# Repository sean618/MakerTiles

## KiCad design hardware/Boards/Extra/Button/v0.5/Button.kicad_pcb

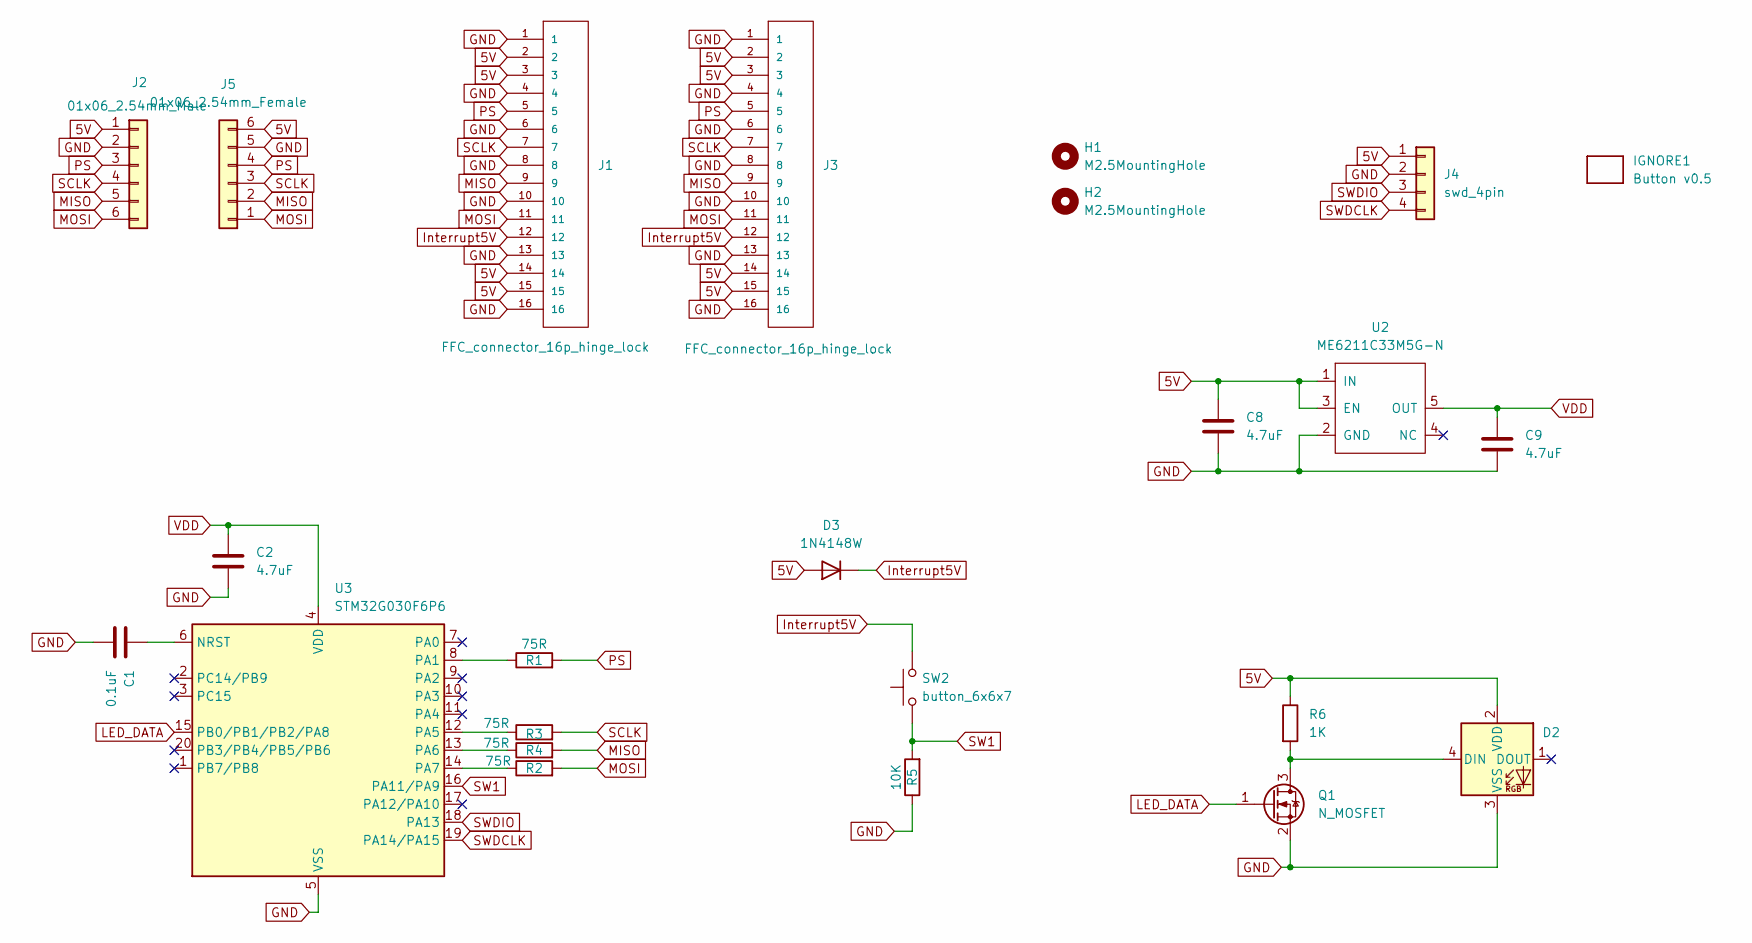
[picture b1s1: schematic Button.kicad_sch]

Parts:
C1: 0.1uF; C_0402_1005Metric
C2, C8, C9: 4.7uF; C_0402_1005Metric
D2: ws2812b_1615; WS2812B_1615
D3: 1N4148W; D_SOD-123
H1, H2: M2.5MountingHole; MountingHole_2.7mm_M2.5_ISO7380
IGNORE1: Button v0.5; BoardText
J1, J3: FFC_connector_16p_hinge_lock
J2: 01x06_2.54mm_Male
J4: swd_4pin; swd_header
J5: 01x06_2.54mm_Female
Q1: N_MOSFET; SOT-23
R1, R2, R3, R4: 75R; R_0402_1005Metric
R5: 10K; R_0402_1005Metric
R6: 1K; R_0402_1005Metric
SW2: button_6x6x7; SW_SPST_PTS645
U2: ME6211C33M5G-N; SOT-23-5
U3: STM32G030F6P6; TSSOP-20_4.4x6.5mm_P0.65mm

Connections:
5V: C8.1, D2.2 (VDD), D3.2 (A), J1.2, J1.3, J1.14, J1.15, J2.1, J3.2, J3.3, J3.14, J3.15, J4.1, J5.6, R6.1, U2.1 (IN), U2.3 (EN)
GND: C1.2, C2.2, C8.2, C9.2, D2.3 (VSS), J1.1, J1.4, J1.6, J1.8, J1.10, J1.13, J1.16, J2.2, J3.1, J3.4, J3.6, J3.8, J3.10, J3.13, J3.16, J4.2, J5.5, Q1.2 (S), R5.1, U2.2 (GND), U3.5 (VSS)
Interrupt5V: D3.1 (K), J1.12, J3.12, SW2.2
LED_DATA: Q1.1 (G), U3.15 (PB0/PB1/PB2/PA8)
MISO: J1.9, J2.5, J3.9, J5.2, R4.2
MOSI: J1.11, J2.6, J3.11, J5.1, R2.2
unnamed: D2.4 (DIN), Q1.3 (D), R6.2
unnamed: C1.1, U3.6 (NRST)
unnamed: R1.1, U3.8 (PA1)
unnamed: R3.1, U3.12 (PA5)
unnamed: R4.1, U3.13 (PA6)
unnamed: R2.1, U3.14 (PA7)
PS: J1.5, J2.3, J3.5, J5.4, R1.2
SCLK: J1.7, J2.4, J3.7, J5.3, R3.2
SW1: R5.2, SW2.1, U3.16 (PA11/PA9)
SWDCLK: J4.4, U3.19 (PA14/PA15)
SWDIO: J4.3, U3.18 (PA13)
VDD: C2.1, C9.1, U2.5 (OUT), U3.4 (VDD)

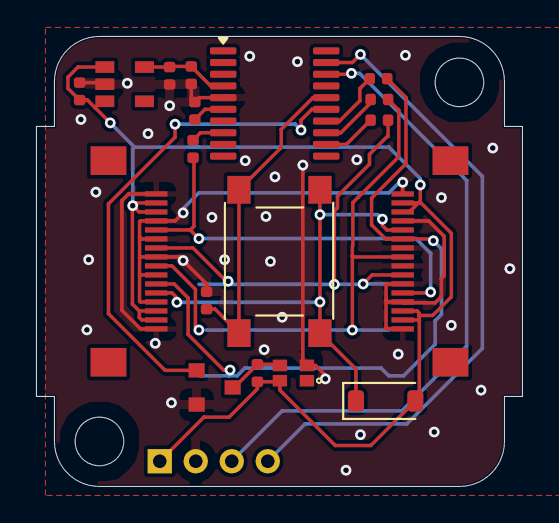
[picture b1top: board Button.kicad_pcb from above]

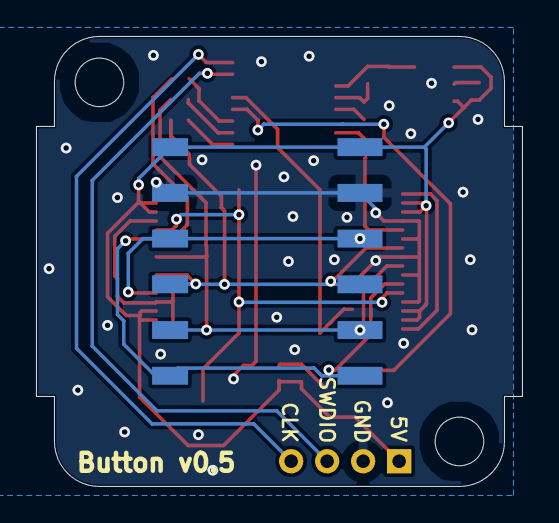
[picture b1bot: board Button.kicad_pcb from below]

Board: 4 copper layers, 27.0 x 25.0 mm, 24 parts (2 on the bottom side), 18 nets.

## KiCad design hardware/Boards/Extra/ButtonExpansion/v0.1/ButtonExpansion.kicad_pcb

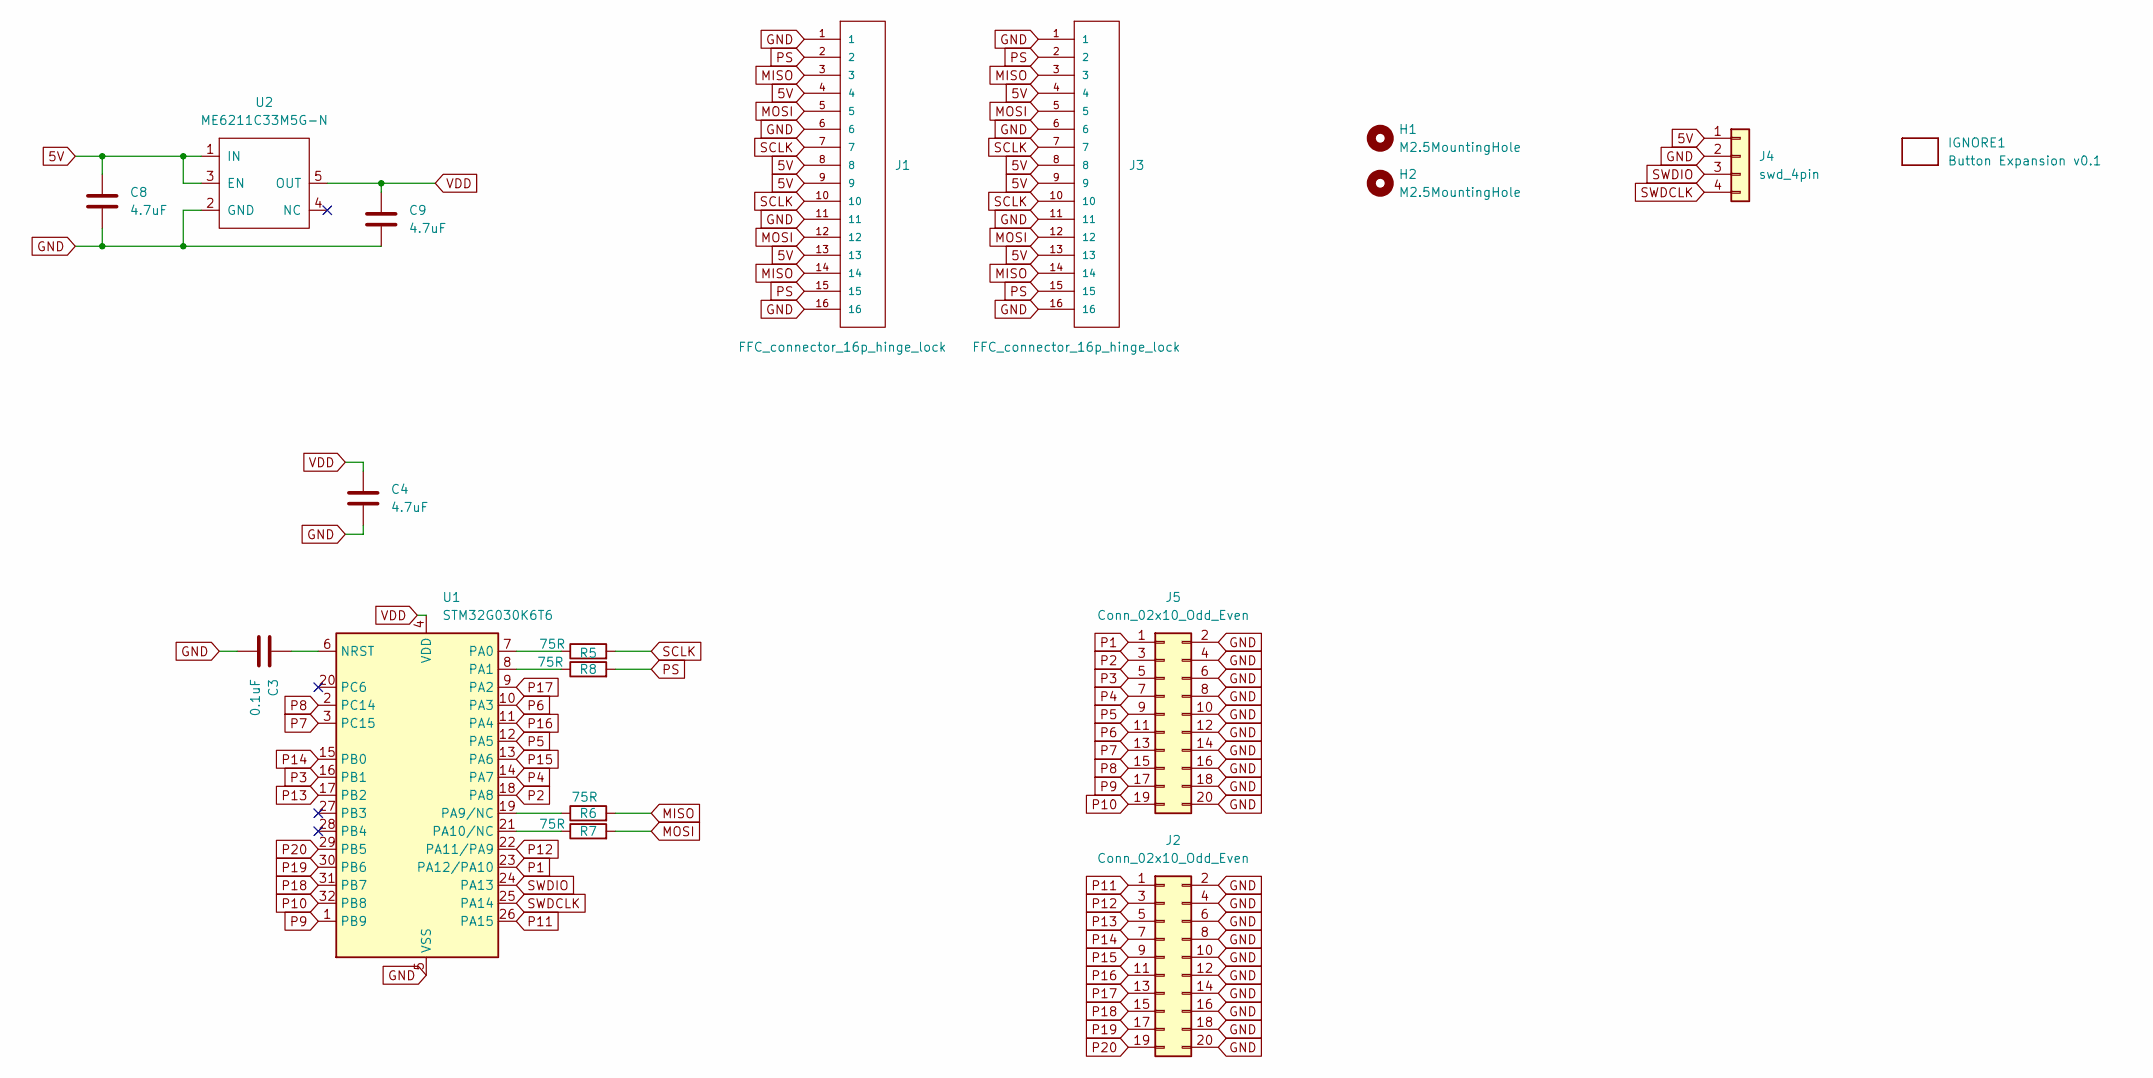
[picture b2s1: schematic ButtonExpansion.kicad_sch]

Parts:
C3: 0.1uF; C_0402_1005Metric
C4, C8, C9: 4.7uF; C_0402_1005Metric
H1, H2: M2.5MountingHole; MountingHole_2.7mm_M2.5_ISO7380
IGNORE1: Button Expansion v0.1; BoardText
J1, J3: FFC_connector_16p_hinge_lock
J2, J5: Conn_02x10_Odd_Even; PinHeader_2x10_P2.54mm_Vertical
J4: swd_4pin; swd_header
R5, R6, R7, R8: 75R; R_0402_1005Metric
U1: STM32G030K6T6; LQFP-32_7x7mm_P0.8mm
U2: ME6211C33M5G-N; SOT-23-5

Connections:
5V: C8.1, J1.4, J1.8, J1.9, J1.13, J3.4, J3.8, J3.9, J3.13, J4.1, U2.1 (IN), U2.3 (EN)
GND: C3.2, C4.2, C8.2, C9.2, J1.1, J1.6, J1.11, J1.16, J2.2, J2.4, J2.6, J2.8, J2.10, J2.12, J2.14, J2.16, J2.18, J2.20, J3.1, J3.6, J3.11, J3.16, J4.2, J5.2, J5.4, J5.6, J5.8, J5.10, J5.12, J5.14, J5.16, J5.18, J5.20, U1.5 (VSS), U2.2 (GND)
MISO: J1.3, J1.14, J3.3, J3.14, R6.2
MOSI: J1.5, J1.12, J3.5, J3.12, R7.2
unnamed: C3.1, U1.6 (NRST)
unnamed: R5.1, U1.7 (PA0)
unnamed: R8.1, U1.8 (PA1)
unnamed: R6.1, U1.19 (PA9/NC)
unnamed: R7.1, U1.21 (PA10/NC)
P1: J5.1, U1.23 (PA12/PA10)
P2: J5.3, U1.18 (PA8)
P3: J5.5, U1.16 (PB1)
P4: J5.7, U1.14 (PA7)
P5: J5.9, U1.12 (PA5)
P6: J5.11, U1.10 (PA3)
P7: J5.13, U1.3 (PC15)
P8: J5.15, U1.2 (PC14)
P9: J5.17, U1.1 (PB9)
P10: J5.19, U1.32 (PB8)
P11: J2.1, U1.26 (PA15)
P12: J2.3, U1.22 (PA11/PA9)
P13: J2.5, U1.17 (PB2)
P14: J2.7, U1.15 (PB0)
P15: J2.9, U1.13 (PA6)
P16: J2.11, U1.11 (PA4)
P17: J2.13, U1.9 (PA2)
P18: J2.15, U1.31 (PB7)
P19: J2.17, U1.30 (PB6)
P20: J2.19, U1.29 (PB5)
PS: J1.2, J1.15, J3.2, J3.15, R8.2
SCLK: J1.7, J1.10, J3.7, J3.10, R5.2
SWDCLK: J4.4, U1.25 (PA14)
SWDIO: J4.3, U1.24 (PA13)
VDD: C4.1, C9.1, U1.4 (VDD), U2.5 (OUT)

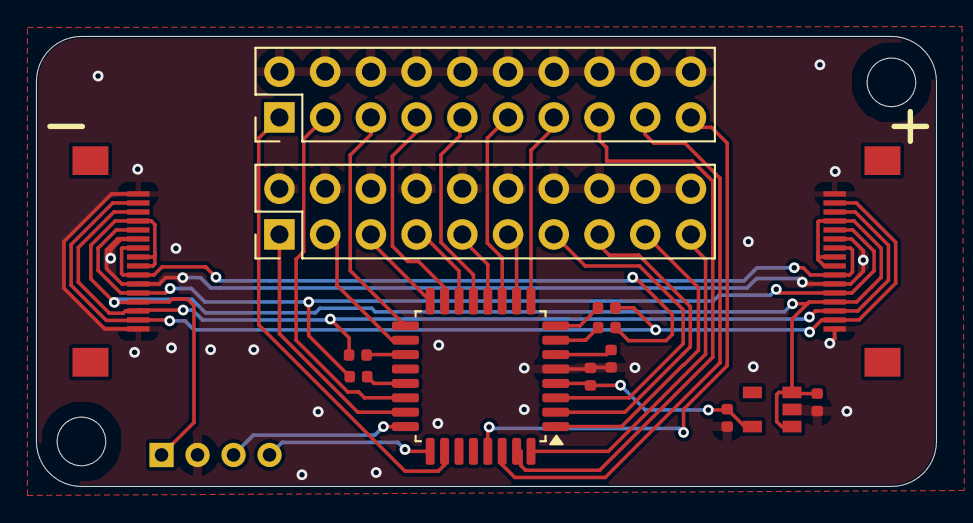
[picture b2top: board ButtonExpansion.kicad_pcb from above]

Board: 2 copper layers, 50.0 x 25.0 mm, 18 parts (0 on the bottom side), 34 nets.

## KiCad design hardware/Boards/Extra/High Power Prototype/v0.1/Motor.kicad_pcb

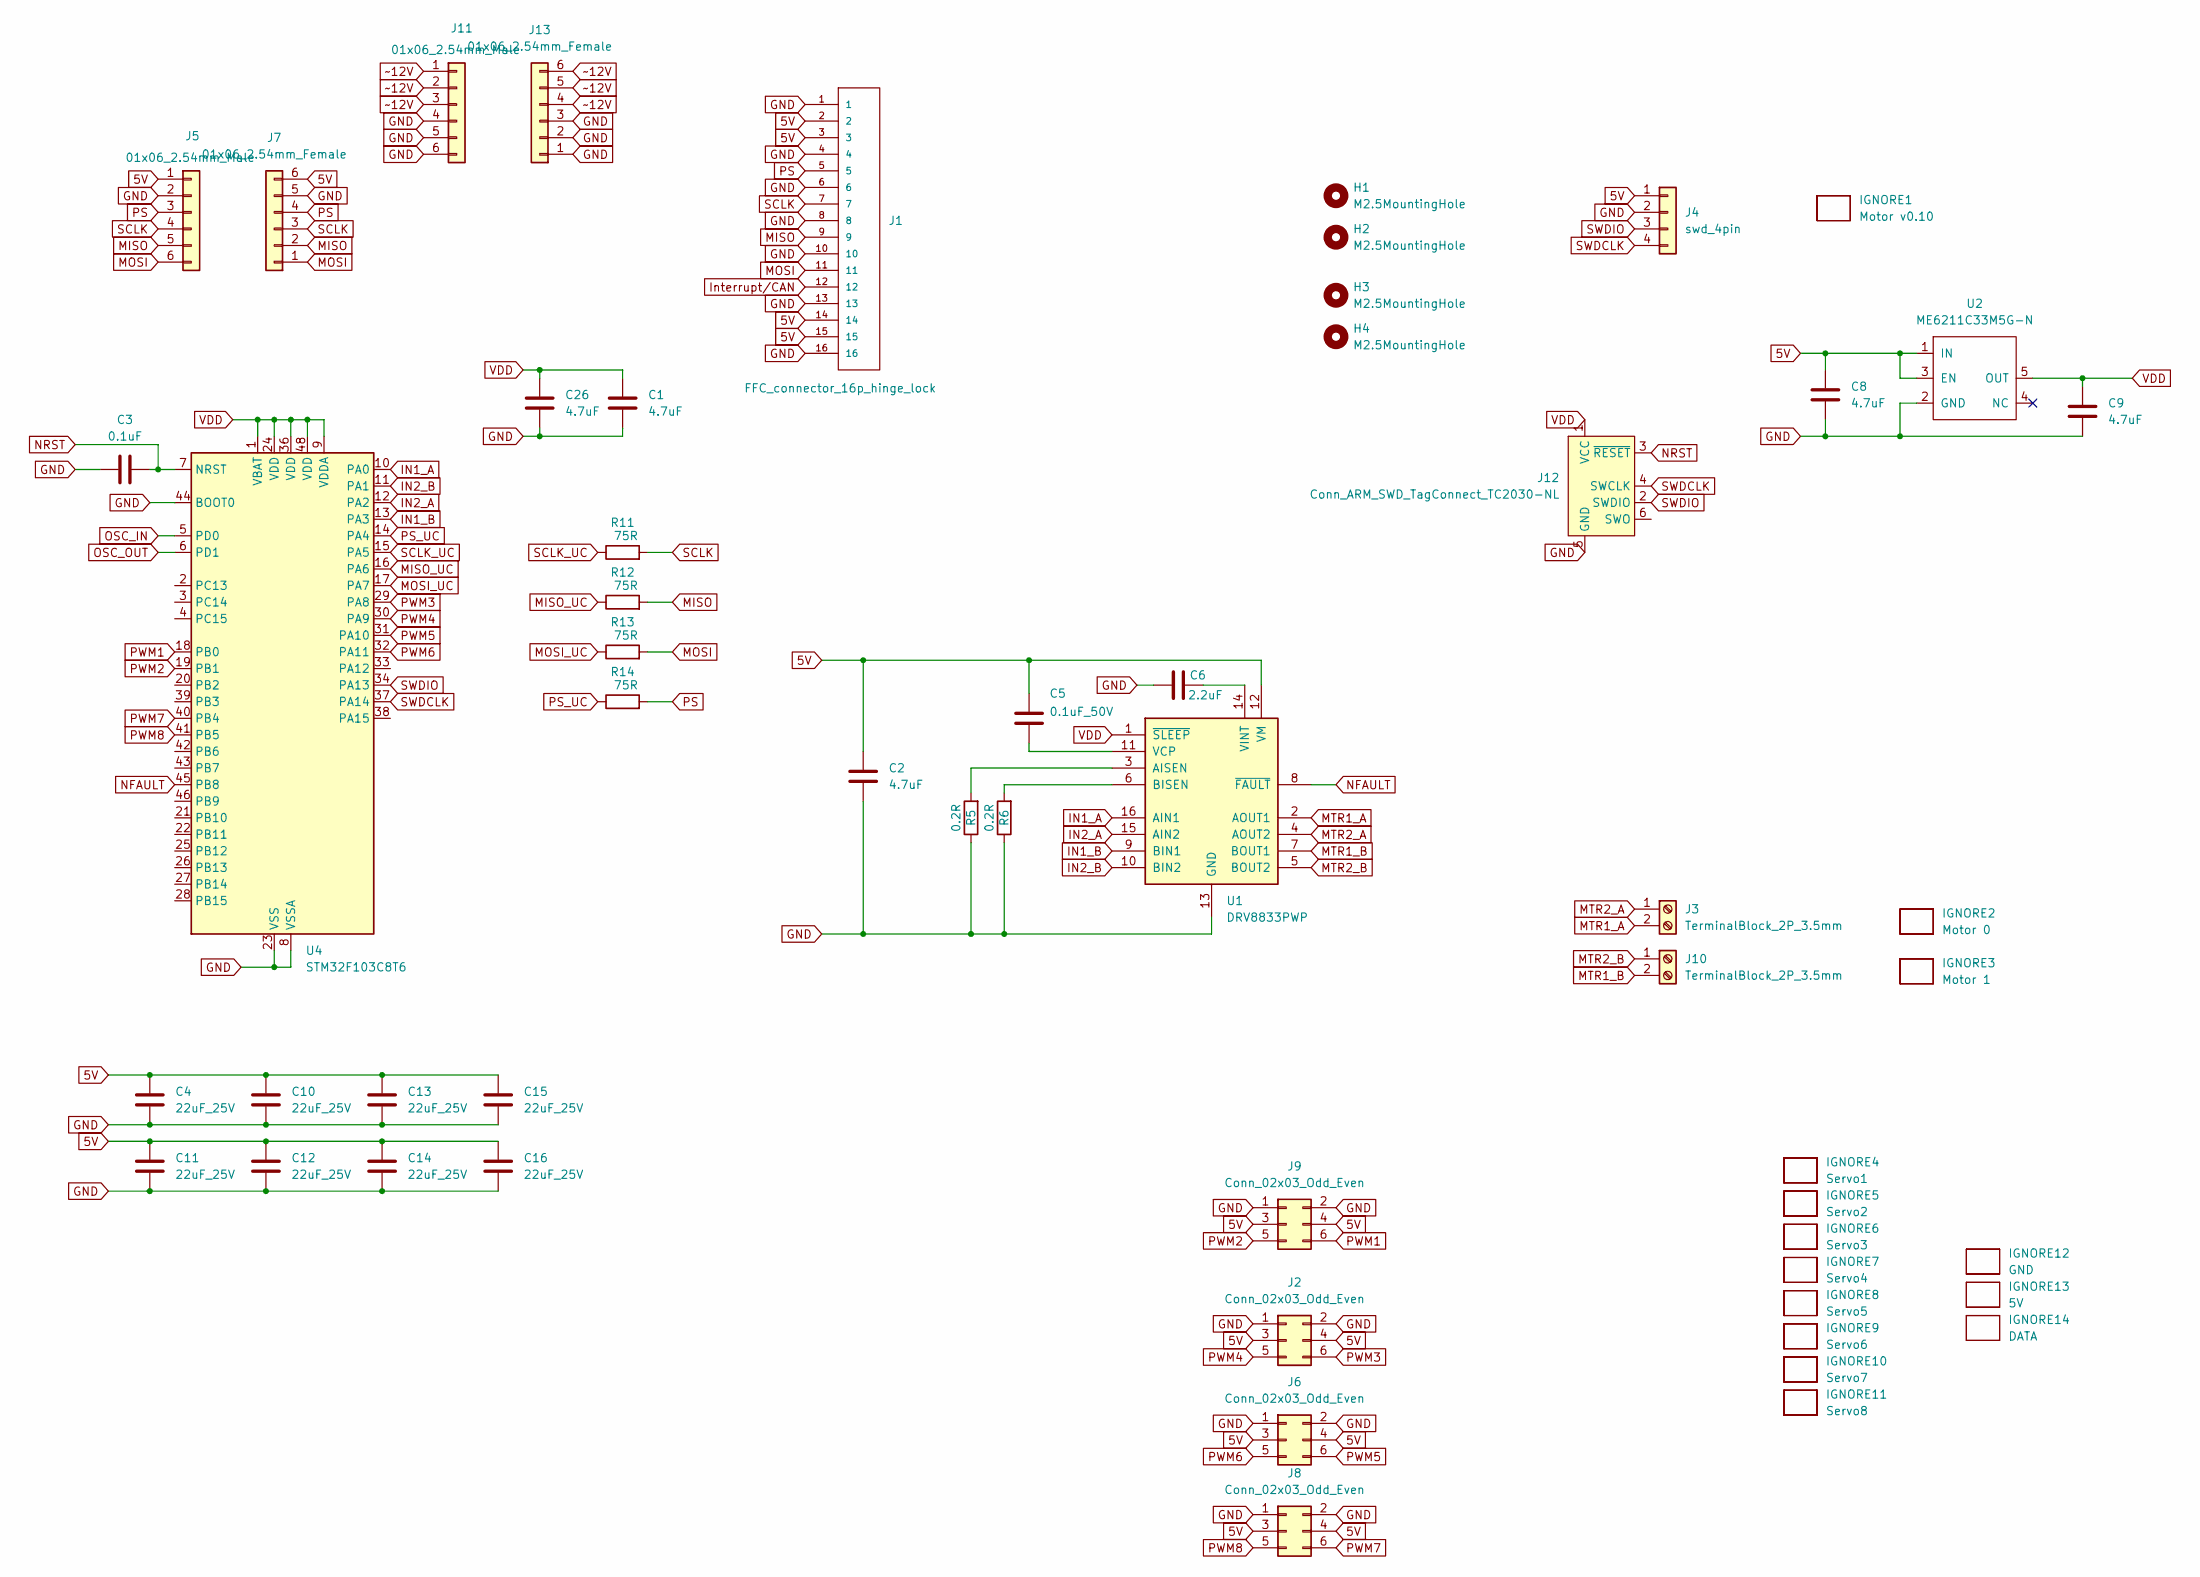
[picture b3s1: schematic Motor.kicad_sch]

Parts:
C1, C2, C8, C9, C26: 4.7uF; C_0402_1005Metric
C3: 0.1uF; C_0402_1005Metric
C4, C10, C11, C12, C13, C14, C15, C16: 22uF_25V; C_0805_2012Metric
C5: 0.1uF_50V; C_0402_1005Metric
C6: 2.2uF; C_0402_1005Metric
H1, H2, H3, H4: M2.5MountingHole; MountingHole_2.7mm_M2.5_ISO7380
IGNORE1: Motor v0.10; BoardText
IGNORE2: Motor 0; BoardText
IGNORE3: Motor 1; BoardText
IGNORE4: Servo1; BoardText
IGNORE5: Servo2; BoardText
IGNORE6: Servo3; BoardText
IGNORE7: Servo4; BoardText
IGNORE8: Servo5; BoardText
IGNORE9: Servo6; BoardText
IGNORE10: Servo7; BoardText
IGNORE11: Servo8; BoardText
IGNORE12: GND; BoardText
IGNORE13: 5V; BoardText
IGNORE14: DATA; BoardText
J1: FFC_connector_16p_hinge_lock
J2, J6, J8, J9: Conn_02x03_Odd_Even; PinHeader_2x03_P2.54mm_Vertical_SMD
J3, J10: TerminalBlock_2P_3.5mm
J4: swd_4pin; swd_header
J5, J11: 01x06_2.54mm_Male
J7, J13: 01x06_2.54mm_Female
J12: Conn_ARM_SWD_TagConnect_TC2030-NL; Tag-Connect_TC2030-IDC-NL_2x03_P1.27mm_Vertical
R5, R6: 0.2R; R_1210_3225Metric
R11, R12, R13, R14: 75R; R_0402_1005Metric
U1: DRV8833PWP; HTSSOP-16-1EP_4.4x5mm_P0.65mm_EP3.4x5mm_Mask2.46x2.31mm_The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
U2: ME6211C33M5G-N; SOT-23-5
U4: STM32F103C8T6; LQFP-48_7x7mm_P0.5mm

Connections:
5V: C2.1, C4.1, C5.1, C8.1, C10.1, C11.1, C12.1, C13.1, C14.1, C15.1, C16.1, J1.2, J1.3, J1.14, J1.15, J2.3, J2.4, J4.1, J5.1, J6.3, J6.4, J7.6, J8.3, J8.4, J9.3, J9.4, U1.12 (VM), U2.1 (IN), U2.3 (EN)
GND: C1.2, C2.2, C3.1, C4.2, C6.1, C8.2, C9.2, C10.2, C11.2, C12.2, C13.2, C14.2, C15.2, C16.2, C26.2, J1.1, J1.4, J1.6, J1.8, J1.10, J1.13, J1.16, J2.1, J2.2, J4.2, J5.2, J6.1, J6.2, J7.5, J8.1, J8.2, J9.1, J9.2, J11.4, J11.5, J11.6, J12.5 (GND), J13.1, J13.2, J13.3, R5.1, R6.1, U1.13 (GND), U1.17 (GND), U2.2 (GND), U4.8 (VSSA), U4.23 (VSS), U4.35 (VSS), U4.44 (BOOT0), U4.47 (VSS)
IN1_A: U1.16 (AIN1), U4.10 (PA0)
IN1_B: U1.9 (BIN1), U4.13 (PA3)
IN2_A: U1.15 (AIN2), U4.12 (PA2)
IN2_B: U1.10 (BIN2), U4.11 (PA1)
Interrupt/CAN: J1.12
MISO: J1.9, J5.5, J7.2, R12.2
MISO_UC: R12.1, U4.16 (PA6)
MOSI: J1.11, J5.6, J7.1, R13.2
MOSI_UC: R13.1, U4.17 (PA7)
MTR1_A: J3.2, U1.2 (AOUT1)
MTR1_B: J10.2, U1.7 (BOUT1)
MTR2_A: J3.1, U1.4 (AOUT2)
MTR2_B: J10.1, U1.5 (BOUT2)
NFAULT: U1.8 (~FAULT), U4.45 (PB8)
NRST: C3.2, J12.3 (~RESET), U4.7 (NRST)
unnamed: R5.2, U1.3 (AISEN)
unnamed: R6.2, U1.6 (BISEN)
unnamed: C5.2, U1.11 (VCP)
unnamed: C6.2, U1.14 (VINT)
OSC_IN: U4.5 (PD0)
OSC_OUT: U4.6 (PD1)
PS: J1.5, J5.3, J7.4, R14.2
PS_UC: R14.1, U4.14 (PA4)
PWM1: J9.6, U4.18 (PB0)
PWM2: J9.5, U4.19 (PB1)
PWM3: J2.6, U4.29 (PA8)
PWM4: J2.5, U4.30 (PA9)
PWM5: J6.6, U4.31 (PA10)
PWM6: J6.5, U4.32 (PA11)
PWM7: J8.6, U4.40 (PB4)
PWM8: J8.5, U4.41 (PB5)
SCLK: J1.7, J5.4, J7.3, R11.2
SCLK_UC: R11.1, U4.15 (PA5)
SWDCLK: J4.4, J12.4 (SWCLK), U4.37 (PA14)
SWDIO: J4.3, J12.2 (SWDIO), U4.34 (PA13)
VDD: C1.1, C9.1, C26.1, J12.1 (VCC), U1.1 (~SLEEP), U2.5 (OUT), U4.1 (VBAT), U4.9 (VDDA), U4.24 (VDD), U4.36 (VDD), U4.48 (VDD)
~12V: J11.1, J11.2, J11.3, J13.4, J13.5, J13.6

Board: 2 copper layers, 55 parts (4 on the bottom side), 36 nets, no tracks yet.

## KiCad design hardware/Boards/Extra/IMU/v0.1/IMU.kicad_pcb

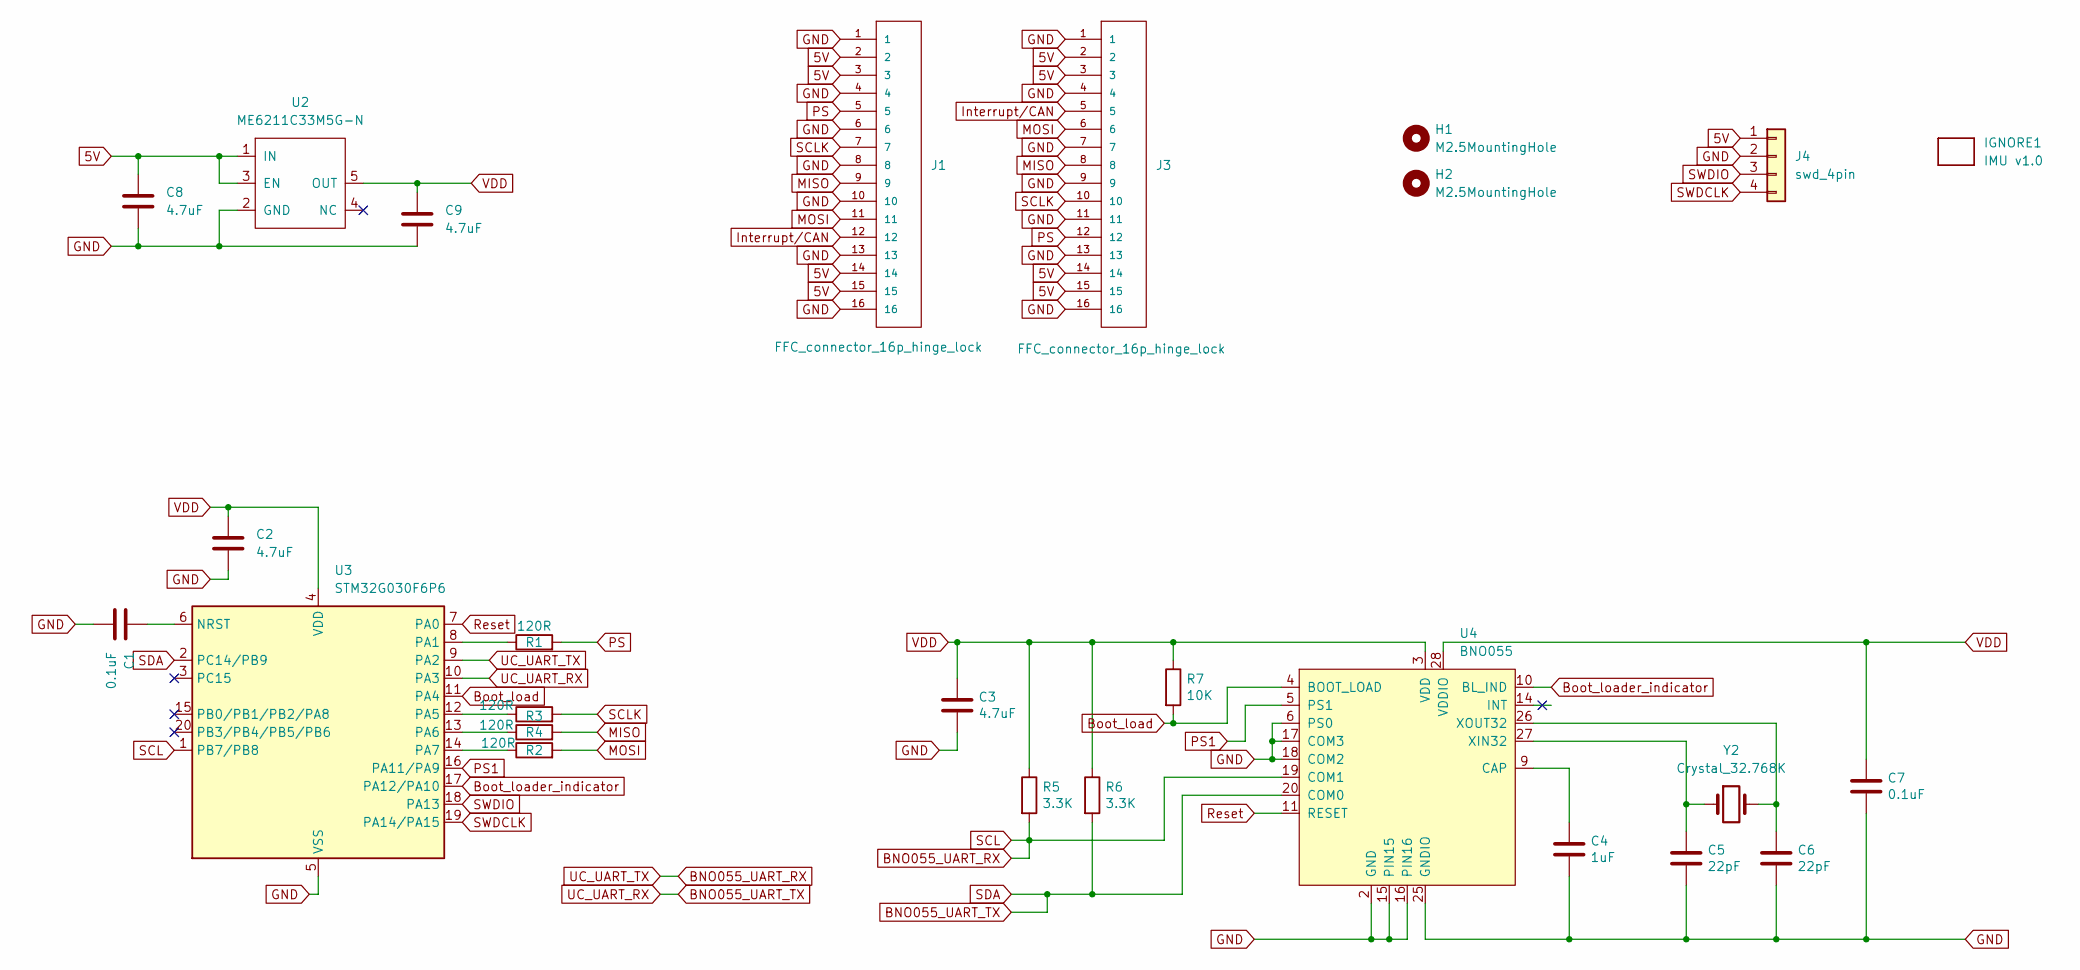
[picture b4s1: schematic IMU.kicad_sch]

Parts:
C1, C7: 0.1uF; C_0402_1005Metric
C2, C3, C8, C9: 4.7uF; C_0402_1005Metric
C4: 1uF; C_0402_1005Metric
C5, C6: 22pF; C_0402_1005Metric
H1, H2: M2.5MountingHole; MountingHole_2.7mm_M2.5_ISO7380
IGNORE1: IMU v1.0; BoardText
J1, J3: FFC_connector_16p_hinge_lock
J4: swd_4pin; swd_header
R1, R2, R3, R4: 120R; R_0402_1005Metric
R5, R6: 3.3K; R_0402_1005Metric
R7: 10K; R_0402_1005Metric
U2: ME6211C33M5G-N; SOT-23-5
U3: STM32G030F6P6; TSSOP-20_4.4x6.5mm_P0.65mm
U4: BNO055; IMU-BNO055; Manufacturer_Part_Number BNO055
Y2: Crystal_32.768K; Crystal_SMD_3215-2Pin_3.2x1.5mm

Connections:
5V: C8.1, J1.2, J1.3, J1.14, J1.15, J3.2, J3.3, J3.14, J3.15, J4.1, U2.1 (IN), U2.3 (EN)
BNO055_UART_RX: R5.2, U3.1 (PB7/PB8), U3.9 (PA2), U4.19 (COM1)
BNO055_UART_TX: R6.2, U3.2 (PC14/PB9), U3.10 (PA3), U4.20 (COM0)
Boot_load: R7.2, U3.11 (PA4), U4.4 (BOOT_LOAD)
Boot_loader_indicator: U3.17 (PA12/PA10), U4.10 (BL_IND)
GND: C1.2, C2.2, C3.2, C4.2, C5.2, C6.2, C7.2, C8.2, C9.2, J1.1, J1.4, J1.6, J1.8, J1.10, J1.13, J1.16, J3.1, J3.4, J3.7, J3.9, J3.11, J3.13, J3.16, J4.2, U2.2 (GND), U3.5 (VSS), U4.2 (GND), U4.6 (PS0), U4.15 (PIN15), U4.16 (PIN16), U4.17 (COM3), U4.18 (COM2), U4.25 (GNDIO)
Interrupt/CAN: J1.12, J3.5
MISO: J1.9, J3.8, R4.2
MOSI: J1.11, J3.6, R2.2
unnamed: C1.1, U3.6 (NRST)
unnamed: R1.1, U3.8 (PA1)
unnamed: R3.1, U3.12 (PA5)
unnamed: R4.1, U3.13 (PA6)
unnamed: R2.1, U3.14 (PA7)
unnamed: C4.1, U4.9 (CAP)
unnamed: C5.1, U4.27 (XIN32), Y2.1
unnamed: C6.1, U4.26 (XOUT32), Y2.2
PS: J1.5, J3.12, R1.2
PS1: U3.16 (PA11/PA9), U4.5 (PS1)
Reset: U3.7 (PA0), U4.11 (RESET)
SCLK: J1.7, J3.10, R3.2
SWDCLK: J4.4, U3.19 (PA14/PA15)
SWDIO: J4.3, U3.18 (PA13)
VDD: C2.1, C3.1, C7.1, C9.1, R5.1, R6.1, R7.1, U2.5 (OUT), U3.4 (VDD), U4.3 (VDD), U4.28 (VDDIO)

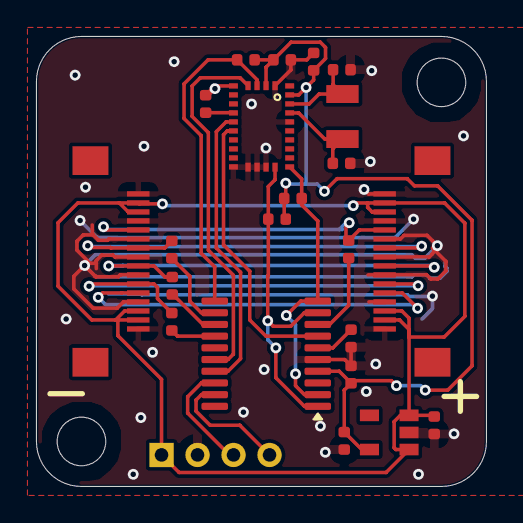
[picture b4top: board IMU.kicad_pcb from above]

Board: 4 copper layers, 25.0 x 25.0 mm, 26 parts (0 on the bottom side), 24 nets.
